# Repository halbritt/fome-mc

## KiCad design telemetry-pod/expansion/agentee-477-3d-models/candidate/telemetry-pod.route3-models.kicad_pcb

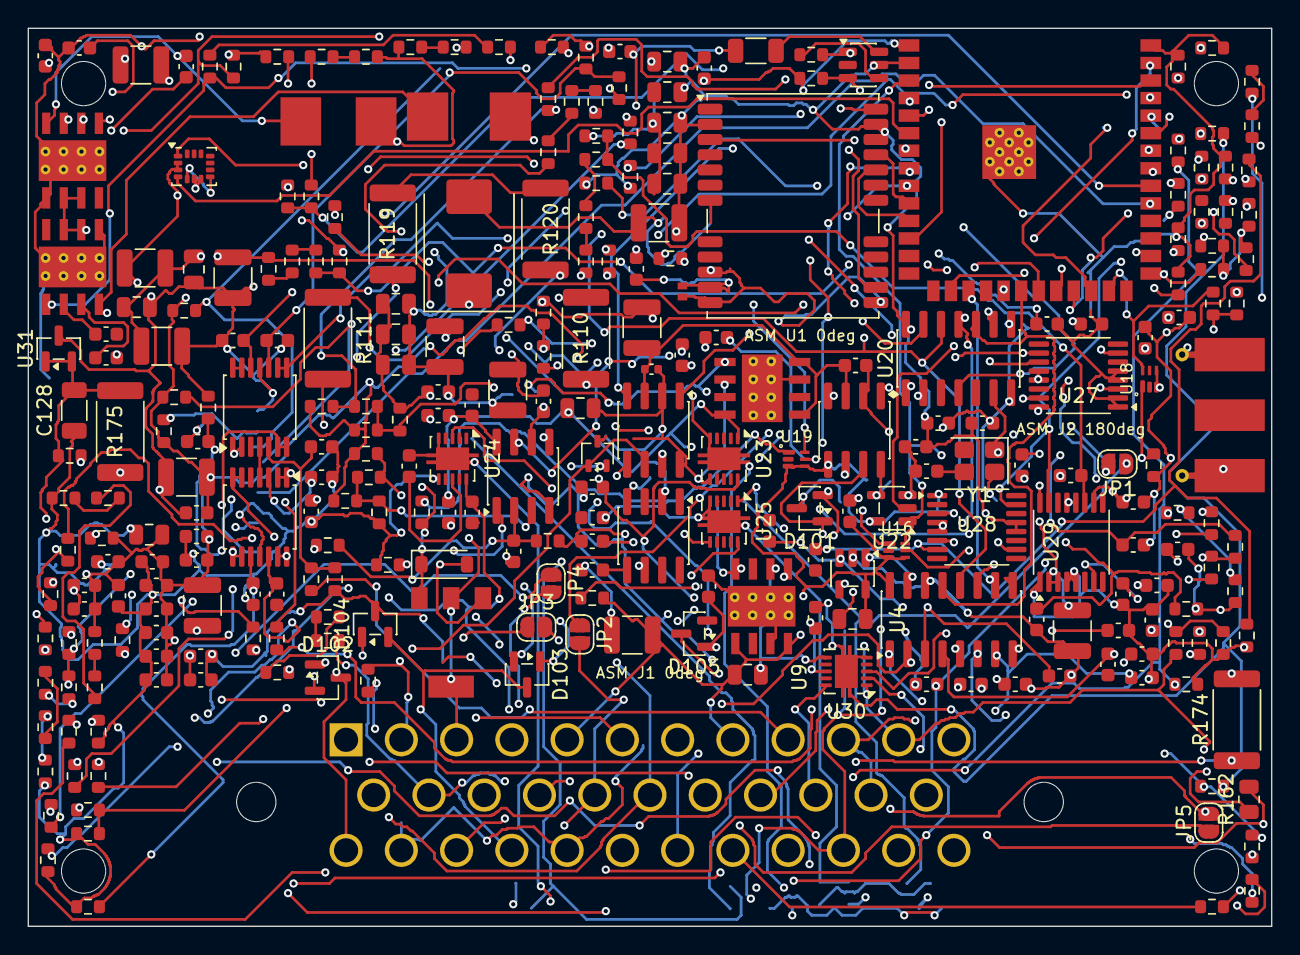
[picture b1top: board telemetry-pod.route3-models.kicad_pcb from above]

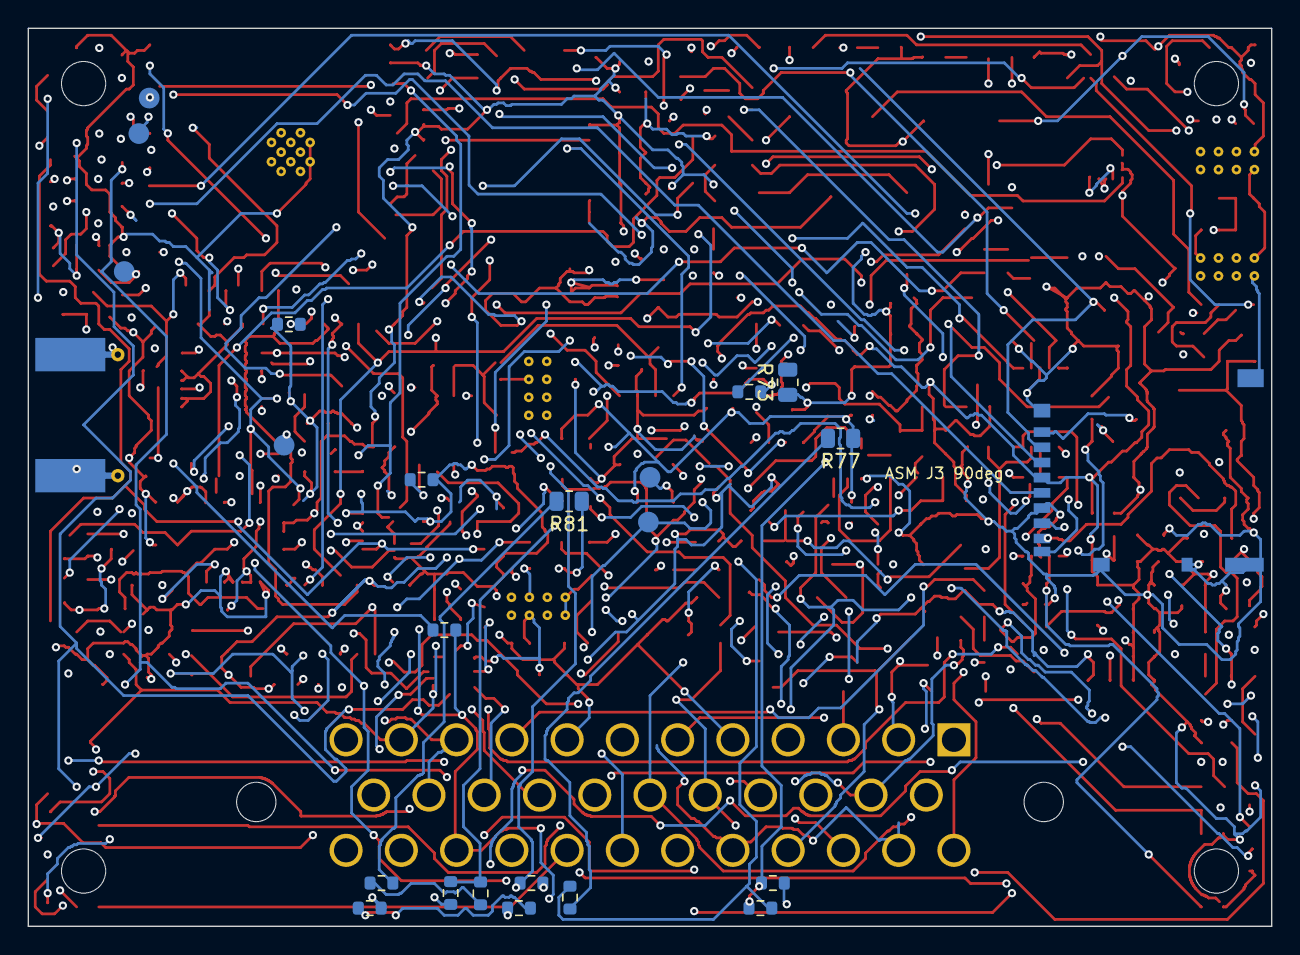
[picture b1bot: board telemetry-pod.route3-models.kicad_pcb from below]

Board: 4 copper layers, 90.0 x 65.0 mm, 309 parts (23 on the bottom side), 182 nets.

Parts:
C1, C2, C8, C9: 4.7 uF/100 V; C_1210_3225Metric
C3, C10: 220 nF/100 V; C_0805_2012Metric
C4, C11, C16, C18, C20, C21, C22, C44: 1 uF/16 V; C_0603_1608Metric
C5, C12, C30, C32, C34, C36, C38, C39, C41, C42, C43, C54, C56, C58, C60: 100 nF/50 V X7R; C_0603_1608Metric
C6, C7, C13, C14, C15, C17, C19: 22 uF/25 V; C_1210_3225Metric
C31, C33, C35, C37, C55, C57, C59, C61: 100 pF C0G/50 V; C_0603_1608Metric
C40: 470 pF C0G/50 V; C_0603_1608Metric
C45: 22uF; C_1210_3225Metric
C46, C48, C49, C51, C53, C62, C65, C72, C76, C78, C79, C83, C84, C85: 100nF; C_0603_1608Metric
C47: 10nF; C_0603_1608Metric
C50, C52, C80: 1uF; C_0603_1608Metric
C64: 4.7 uF/16 V X7R; C_0805_2012Metric
C71, C75, C77: 22nF; C_0603_1608Metric
C81, C82: 18pF C0G; C_0603_1608Metric
C86, C89, C92, C98, C118, C119, C120, C121, C122, C123, C124: 1uF 50V X7R; C_0805_2012Metric
C87, C90, C93, C97, C110, C111, C112, C114, C115, C116, C117, C125, C127, C129: 100nF 50V X7R; C_0603_1608Metric
C88, C91, C94, C126: 10nF 50V C0G 10%; C_0603_1608Metric
C95, C96: 220pF C0G; C_0603_1608Metric
C100: 100n; C_0402_1005Metric
C128: 10uF 16V X7R; C_1206_3216Metric
D1: SMCJ24CA; D_SMC
D2: BZT52C12-7-F; D_SOD-123
D3: PESD5V0C1BLS-QYL; SOD882BD
D100: PESD1CAN-UX; SOT-323_SC-70
D101, D104: PESD2CANFD24V-TR; SOT-23
D102, D103, D105: BAV199,215; SOT-23
H1, H2, H3, H4: MountingHole; AgentEE_Mechanical_MountingHole_NPTH
J1: 1-776163-1; AMPSEAL_35_1-776163-1
J2: 732511150; SMA_Molex_73251-1153_EdgeMount_Horizontal
J3: DM3AT-SF-PEJM5; microSD_HC_Hirose_DM3AT-SF-PEJM5
JP1: TIRE_TERM_CLOSE_ONLY_AT_BUS_END; SolderJumper-2_P1.3mm_Open_RoundedPad1.0x1.5mm
JP2: AUX1_THERM_PULLUP_CLOSE_TO_ENABLE; SolderJumper-2_P1.3mm_Open_RoundedPad1.0x1.5mm
JP3: AUX2_THERM_PULLUP_CLOSE_TO_ENABLE; SolderJumper-2_P1.3mm_Open_RoundedPad1.0x1.5mm
JP4: AUX3_THERM_PULLUP_CLOSE_TO_ENABLE; SolderJumper-2_P1.3mm_Open_RoundedPad1.0x1.5mm
JP5: AUX4_THERM_PULLUP_CLOSE_TO_ENABLE; SolderJumper-2_P1.3mm_Open_RoundedPad1.0x1.5mm
L1: 15 uH; SRP7050TA
L2: 6.8 uH; SRP7050WA
L3: LQW18AN56NJ00D; L_0603_1608Metric
Q1: DMP6023LE-13; DMP6023LE_SOT223
R1, R24, R25, R29: 100 kohm; R_0603_1608Metric
R2: 51 kohm; R_0603_1608Metric
R3, R5, R10, R11, R13, R14, R16, R17, R19, R20, R22, R23, R34, R35, R37, R38, R40, R41, R43, R44, R46, R47, R48, R49, R50, R55, R64, R65, R66, R67, R68, R69, R71, R72: 10 kohm; R_0603_1608Metric
R4: 22 kohm; R_0603_1608Metric
R6: 47 kohm; R_0603_1608Metric
R7: 1 ohm; R_0603_1608Metric
R12, R15, R18, R21, R36, R39, R42, R45, R118, R127: 100 ohm; R_0603_1608Metric
R26: 10 ohm/0.25 W; R_1206_3216Metric
R27: 2 kohm; R_0603_1608Metric
R28: 1 kohm; R_0603_1608Metric
R30, R31, R32, R33: 10k; R_0603_1608Metric
R56: 16.9 kohm 0.1%; R_0603_1608Metric
R57, R61, R63, R112, R113, R115, R121, R122, R124: 10 kohm 0.1%; R_0603_1608Metric
R60: 30.1 kohm 0.1% 25ppm/K; R_0603_1608Metric
R62: 64.9 kohm 0.1%; R_0603_1608Metric
R70: 120 ohm; R_0603_1608Metric
R73, R77, R81, R162: 1.05 Mohm 0.1% 25ppm/K; R_0805_2012Metric
R74, R78, R82: 68.1 kohm 0.1% 25ppm/K; R_0603_1608Metric
R75, R79, R83: 215 kohm 0.1% 25ppm/K; R_0603_1608Metric
R76, R80: 44.2 kohm 0.1%; R_0603_1608Metric
R84: 26.7 kohm 0.1%; R_0603_1608Metric
R100: 120; R_0603_1608Metric
R110, R111, R119, R120: 620 ohm; R_2512_6332Metric
R114, R123: 56 kohm 0.1%; R_0603_1608Metric
R116, R125: 100 kohm 0.1%; R_0603_1608Metric
R117, R126: 4.7 kohm 1%; R_0603_1608Metric
R128, R129, R130, R132, R133, R134, R136, R137, R138, R144, R145, R146, R148, R149, R150, R152, R153, R154, R156, R157, R158, R166, R167, R168: 499 kohm 0.1% 25ppm/C; R_0603_1608Metric
R131, R135, R139, R147, R151, R155, R159, R169: 4.99 kohm 0.1% 25ppm/C; R_0603_1608Metric
R160, R161: 2.2 kohm 1% 100ppm/C; R_0603_1608Metric
R163: 95.3 kohm 0.1% 25ppm/K; R_0603_1608Metric
R164: 287 kohm 0.1% 25ppm/K; R_0603_1608Metric
R165: 44.2 kohm 0.1% 25ppm/K; R_0603_1608Metric
R170, R171, R172, R173: 10 kohm 0.1% 25ppm/K; R_0603_1608Metric
R174, R175: 200 ohm 1% 100ppm/K 1.5W CRCW2512-HP; R_2512_6332Metric
R176, R177, R178: 499 kohm 0.1% 25ppm/K; R_0603_1608Metric
R179: 4.99 kohm 0.1% 25ppm/K; R_0603_1608Metric
R180: 100 kohm 1% 100ppm/K; R_0603_1608Metric
R181: 1.2 kohm 0.1% 25ppm/K; R_0603_1608Metric
TP1: POD_UART_TX; PogoPad_D1.5mm
TP2: POD_UART_RX; PogoPad_D1.5mm
TP3: GND; PogoPad_D1.5mm
TP4: MCU_EN; PogoPad_D1.5mm
TP5: MCU_BOOT; PogoPad_D1.5mm
TP6: +3V3; PogoPad_D1.5mm
U1: ESP32-S3-WROOM-1-N8; ESP32-S3-WROOM-1
U2: LSM6DSO32TR; LGA-14_3x2.5mm_P0.5mm_LayoutBorder3x4y
U3: NEO-M9N-00B; ublox_NEO
U4: MCP3208-BI/SL; SOIC-16_3.9x9.9mm_P1.27mm
U5, U7: LMR36520ADDAR; DDA0008B
U6, U12: TPS7B4253QDDARQ1; DDA0008J_C02
U8, U13: ADA4096-4ARUZ-R7; TSSOP-14_4.4x5mm_P0.65mm
U9: OPA320AIDBVR; SOT-23-5
U10: TPS2553QDBVRQ1; SOT-23-6
U11: REF5050AIDR; SOIC-8_3.9x4.9mm_P1.27mm
U16, U18, U19: TPS389001DSER; DSE0006A
U20: MCP2518FDT-E/SL; SOIC-14_3.9x8.7mm_P1.27mm
U21: TJA1051T/3/1J; SOIC-8_3.9x4.9mm_P1.27mm
U22: SN74LVC1G132DBVR; SOT-23-5
U23, U24, U25, U30: TPS26625DRCR; VSON-10-1EP_3x3mm_P0.5mm_EP1.65x2.4mm
U26: LM2903BQDRQ1; SOIC-8_3.9x4.9mm_P1.27mm
U27, U28, U29: ADS1119IPWR; TSSOP-16_4.4x5mm_P0.65mm
U31: TL431BQDBZR; SOT-23
U100: TJA1051T-3; SOIC-8_3.9x4.9mm_P1.27mm
Y1: X1E0003410031 20MHz 12pF; Crystal_SMD_SeikoEpson_FA238-4Pin_3.2x2.5mm

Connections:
/+3V3: C13.1, C14.1, C15.1, C38.1, C41.1, C43.1, C44.1, C45.1, C46.1, C48.1, C49.1, C50.1, C51.1, C52.1, C53.1, C62.1, C64.1, C65.1, C72.1, C76.1, C78.1, C79.1, C80.1, C84.1, C85.1, C118.1, C119.1, C120.1, C121.1, C122.1, C123.1, J3.4, L2.2, R4.1, R25.2, R29.1, R30.1, R31.1, R32.1, R46.1, R47.1, R48.1, R49.1, R50.1, R55.2, R56.1, R64.1, R65.1, R66.1, R67.1, R69.1, R71.1, R114.1, R117.1, R123.1, R126.1, R136.1, R160.1, R161.1, TP6.1, U1.2, U2.5, U2.8, U3.2, U3.22, U3.23, U4.16, U8.4, U9.5, U10.1, U10.5, U13.4, U16.3, U16.4, U18.3, U18.4, U19.3, U19.4, U20.14, U21.5, U22.5, U27.3, U27.12, U27.13, U28.1, U28.3, U28.12, U28.13, U29.2, U29.3, U29.12, U29.13, U100.5
/+5V_CAN: C19.1, C83.1, C100.1, U12.1, U12.4, U21.3, U100.3
/ADC_AIN0: C31.1, R12.2, U4.1
/ADC_AIN1: C33.1, R15.2, U4.2
/ADC_AIN2: C35.1, R18.2, U4.3
/ADC_AIN3: C37.1, R21.2, U4.4
/ADC_AIN4: C55.1, R36.2, U4.5
/ADC_AIN5: C57.1, R39.2, U4.6
/ADC_AIN6: C59.1, R42.2, U4.7
/ADC_AIN7: C61.1, R45.2, U4.8
/ADC_CS: R32.2, U1.17, U4.10
/AFE_BUF0: R12.1, U8.1, U8.2
/AFE_BUF1: R15.1, U8.6, U8.7
/AFE_BUF2: R18.1, U8.8, U8.9
/AFE_BUF3: R21.1, U8.13, U8.14
/AFE_BUF4: R36.1, U13.1, U13.2
/AFE_BUF5: R39.1, U13.6, U13.7
/AFE_BUF6: R42.1, U13.8, U13.9
/AFE_BUF7: R45.1, U13.13, U13.14
/AFE_DIV0: C30.1, R10.2, R11.1, U8.3
/AFE_DIV1: C32.1, R13.2, R14.1, U8.5
/AFE_DIV2: C34.1, R16.2, R17.1, U8.10
/AFE_DIV3: C36.1, R19.2, R20.1, U8.12
/AFE_DIV4: C54.1, R34.2, R35.1, U13.3
/AFE_DIV5: C56.1, R37.2, R38.1, U13.5
/AFE_DIV6: C58.1, R40.2, R41.1, U13.10
/AFE_DIV7: C60.1, R43.2, R44.1, U13.12
/ANT_BIAS: C42.1, L3.1, R26.2
/ANT_LIMITED: R26.1, U10.6
/BOOT_3V3: C12.1, U7.7
/BOOT_PRE: C5.1, U5.7
/DIAG_I2C_SCL: R161.2, U1.23, U27.16, U28.16, U29.16
/DIAG_I2C_SDA: R160.2, U1.22, U27.15, U28.15, U29.15
/DIAG_U27_AIN0: C110.1, R130.2, R131.1, U27.11
/DIAG_U27_AIN0_UPPER1: R128.2, R129.1
/DIAG_U27_AIN0_UPPER2: R129.2, R130.1
/DIAG_U27_AIN1: C111.1, R134.2, R135.1, U27.10
/DIAG_U27_AIN1_UPPER1: R132.2, R133.1
/DIAG_U27_AIN1_UPPER2: R133.2, R134.1
/DIAG_U27_AIN2: C112.1, R138.2, R139.1, U27.7
/DIAG_U27_AIN2_UPPER1: R136.2, R137.1
/DIAG_U27_AIN2_UPPER2: R137.2, R138.1
/DIAG_U28_AIN1: C114.1, R146.2, R147.1, U28.10
/DIAG_U28_AIN1_UPPER1: R144.2, R145.1
/DIAG_U28_AIN1_UPPER2: R145.2, R146.1
/DIAG_U28_AIN2: C127.1, R168.2, R169.1, U28.7
/DIAG_U28_AIN2_UPPER1: R166.2, R167.1
/DIAG_U28_AIN2_UPPER2: R167.2, R168.1
/DIAG_U28_AIN3: C129.1, R178.2, R179.1, U28.6
/DIAG_U28_AIN3_UPPER1: R176.2, R177.1
/DIAG_U28_AIN3_UPPER2: R177.2, R178.1
/DIAG_U29_AIN0: C115.1, R150.2, R151.1, U29.11
/DIAG_U29_AIN0_UPPER1: R148.2, R149.1
/DIAG_U29_AIN0_UPPER2: R149.2, R150.1
/DIAG_U29_AIN1: C116.1, R154.2, R155.1, U29.10
/DIAG_U29_AIN1_UPPER1: R152.2, R153.1
/DIAG_U29_AIN1_UPPER2: R153.2, R154.1
/DIAG_U29_AIN2: C117.1, R158.2, R159.1, U29.7
/DIAG_U29_AIN2_UPPER1: R156.2, R157.1
/DIAG_U29_AIN2_UPPER2: R157.2, R158.1
/FB_3V3: R5.1, R28.2, U7.5
/FB_3V3_SERIES: R4.2, R28.1
/FB_PRE: R3.1, R27.2, U5.5
/FB_PRE_SERIES: R2.2, R27.1
/GND: C1.2, C2.2, C3.2, C4.2, C6.2, C7.2, C8.2, C9.2, C10.2, C11.2, C13.2, C14.2, C15.2, C16.2, C17.2, C18.2, C19.2, C20.2, C21.2, C22.2, C30.2, C31.2, C32.2, C33.2, C34.2, C35.2, C36.2, C37.2, C38.2, C39.2, C40.2, C41.2, C42.2, C43.2, C44.2, C45.2, C46.2, C47.2, C48.2, C49.2, C50.2, C51.2, C52.2, C53.2, C54.2, C55.2, C56.2, C57.2, C58.2, C59.2, C60.2, C61.2, C62.2, C64.2, C65.2, C71.2, C72.2, C75.2, C76.2, C77.2, C78.2, C79.2, C80.2, C81.2, C82.2, C83.2, C84.2, C85.2, C86.2, C87.2, C89.2, C90.2, C92.2, C93.2, C95.2, C96.2, C97.2, C98.2, C100.2, C110.2, C111.2, C112.2, C114.2, C115.2, C116.2, C117.2, C118.2, C119.2, C120.2, C121.2, C122.2, C123.2, C124.2, C125.2, C127.2, C128.2, C129.2, D1.2, D3.2, D100.3, D101.3, D104.3, J1.4, J1.7, J1.10, J1.13, J1.16, J1.22, J1.25, J1.28, J1.32, J2.2, J3.6, J3.10, J3.SH, R1.2, R3.2, R5.2, R6.2, R11.2, R14.2, R17.2, R20.2, R23.2, R24.2, R33.2, R35.2, R38.2, R41.2, R44.2, R57.2, R61.2, R63.2, R68.2, R72.2, R113.2, R115.2, R122.2, R124.2, R131.2, R135.2, R139.2, R147.2, R151.2, R155.2, R159.2, R169.2, R179.2, R180.2, TP3.1, U1.1, U1.40, U1.41, U2.2, U2.3, U2.6, U2.7, U3.7, U3.10, U3.12, U3.13, U3.24, U4.9, U4.14, U5.1, U5.9, U6.3, U6.6, U6.9, U7.1, U7.9, U8.11, U9.2, U10.2, U11.4, U12.3, U12.6, U12.9, U13.11, U16.2, U18.2, U19.2, U20.7, U21.2, U22.3, U23.6, U24.6, U25.6, U26.4, U27.1, U27.2, U27.4, U27.5, U28.2, U28.4, U28.5, U29.1, U29.4, U29.5, U30.6, U31.3, U100.2, U100.8, Y1.2, Y1.4
/GNSS_ANT_FAULT_N: R25.1, U10.4
/GNSS_LNA_EN: R24.1, U3.14, U10.3
/GNSS_PPS: U1.7, U3.3
/GNSS_RX_IN: U1.10, U3.21
/GNSS_TX_OUT: U1.11, U3.20
/IMU_CS: R31.2, U1.18, U2.12
/IMU_INT1: U1.6, U2.4
/MCU_BOOT: R30.2, TP5.1, U1.27
/MCU_BOOT46: R33.1, U1.16
/MCU_EN: C47.1, R29.2, TP4.1, U1.3, U16.6, U22.1
/POD_5V_AUX: C125.1, D105.1, J1.21, R166.1, R180.1, U30.10
/POD_5V_SENSOR: C17.1, C124.1, J1.5, J1.8, J1.11, J1.14, R6.1, R22.1, R60.1, R144.1, R162.1, U6.1, U6.4, U30.1
/POD_12V_IN: D1.1, J1.3, Q1.2
/POD_12V_PROTECTED: C1.1, C2.1, C3.1, C8.1, C9.1, C10.1, D2.1, Q1.3, R62.1, R128.1, U5.2, U5.3, U7.2, U7.3
/POD_AUX1_SIGNAL: J1.17, JP2.2, R34.1
/POD_AUX2_SIGNAL: J1.18, JP3.2, R37.1
/POD_AUX3_SIGNAL: J1.19, JP4.2, R40.1
/POD_AUX4_SIGNAL: J1.20, JP5.2, R43.1
/POD_CAN_N: D100.1, J1.2, R100.2, U100.6
/POD_CAN_P: D100.2, J1.1, R100.1, U100.7
/POD_FRONT_BRAKE_SIGNAL: J1.12, R16.1
/POD_FRONT_FORK_SIGNAL: J1.6, R10.1
/POD_GNSS_RF: D3.1, J2.1, L3.2, U3.11
/POD_REAR_BRAKE_SIGNAL: J1.15, R19.1
/POD_REAR_SHOCK_SIGNAL: J1.9, R13.1
/POD_TIRE_SUPPLY: C93.1, J1.31, R156.1, U25.10
/POD_UART_RX: TP2.1, U1.36
/POD_UART_TX: TP1.1, U1.37
/POD_WHEEL_FRONT_SIGNAL: D102.3, D104.1, J1.24
/POD_WHEEL_FRONT_SUPPLY: C87.1, J1.23, R110.1, R148.1, U23.10
/POD_WHEEL_REAR_SIGNAL: D103.3, D104.2, J1.27
/POD_WHEEL_REAR_SUPPLY: C90.1, J1.26, R119.1, R152.1, U24.10
/POWER_FAIL_N: R65.2, U1.12, U19.6
/PRE_6V3: C6.1, C7.1, C16.1, C18.1, C20.1, C86.1, C89.1, C92.1, C97.1, C98.1, L1.2, R2.1, R73.1, R77.1, R81.1, R132.1, U6.8, U11.2, U12.8, U23.1, U24.1, U25.1, U26.8
/REF_CAP_NODE: C22.1, R7.2
/REF_DIV: C39.1, R22.2, R23.1, U9.3
/REF_NR: C21.1, U11.5
/REVERSE_GATE: D2.2, Q1.1, R1.1
/SD_CD: J3.9, R55.1, U1.28
/SD_CLK: J3.5, U1.31
/SD_CMD: J3.3, R46.2, U1.32
/SD_DAT0: J3.7, R47.2, U1.33
/SD_DAT1: J3.8, R48.2, U1.34
/SD_DAT2: J3.1, R49.2, U1.35
/SD_DAT3: J3.2, R50.2, U1.24
/SENSOR_FAULT_N: R64.2, U1.25, U18.6
/SENSOR_POWER_AUX_DVDT: C126.1, U30.8
/SENSOR_POWER_AUX_ILIM: R165.1, U30.7
/SENSOR_POWER_AUX_OVP: R163.2, R164.1, U30.3
/SENSOR_POWER_AUX_RTN: C126.2, R164.2, R165.2, U30.5, U30.11
/SENSOR_POWER_AUX_UVLO: R162.2, R163.1, U30.2
/SENSOR_POWER_FRONT_DVDT: C88.1, U23.8
/SENSOR_POWER_FRONT_ILIM: R76.1, U23.7
/SENSOR_POWER_FRONT_OVP: R74.2, R75.1, U23.3
/SENSOR_POWER_FRONT_RTN: C88.2, R75.2, R76.2, U23.5, U23.11
/SENSOR_POWER_FRONT_UVLO: R73.2, R74.1, U23.2
/SENSOR_POWER_REAR_DVDT: C91.1, U24.8
/SENSOR_POWER_REAR_ILIM: R80.1, U24.7
/SENSOR_POWER_REAR_OVP: R78.2, R79.1, U24.3
/SENSOR_POWER_REAR_RTN: C91.2, R79.2, R80.2, U24.5, U24.11
/SENSOR_POWER_REAR_UVLO: R77.2, R78.1, U24.2
/SENSOR_POWER_TIRE_DVDT: C94.1, U25.8
/SENSOR_POWER_TIRE_ILIM: R84.1, U25.7
/SENSOR_POWER_TIRE_OVP: R82.2, R83.1, U25.3
/SENSOR_POWER_TIRE_RTN: C94.2, R83.2, R84.2, U25.5, U25.11
/SENSOR_POWER_TIRE_UVLO: R81.2, R82.1, U25.2
/SENSOR_REF_2V5: C40.1, U4.15, U9.1, U9.4
/SETPOINT_5V: R7.1, U6.5, U11.6, U12.5
/SPI_MISO: U1.21, U2.1, U4.12, U20.12
/SPI_MOSI: U1.19, U2.14, U4.11, U20.11
/SPI_SCK: U1.20, U2.13, U4.13, U20.10
/SUP_U16_CT: C71.1, U16.5
/SUP_U16_SENSE: R56.2, R57.1, U16.1
/SUP_U18_CT: C75.1, U18.5
/SUP_U18_SENSE: R61.1, R181.2, U18.1
/SUP_U18_TOP_SERIES: R60.2, R181.1
/SUP_U19_CT: C77.1, U19.5
/SUP_U19_SENSE: R62.2, R63.1, U19.1
/SW_3V3: C12.2, L2.1, U7.8
/SW_PRE: C5.2, L1.1, U5.8
/THERM_AUX1_SELECT: JP2.1, R170.2
/THERM_AUX2_SELECT: JP3.1, R171.2
/THERM_AUX3_SELECT: JP4.1, R172.2
/THERM_AUX4_SELECT: JP5.1, R173.2
/THERM_BIAS_IN: D105.3, R174.1
/THERM_BIAS_MID: R174.2, R175.1
/THERM_EXC_2V495: C128.1, R170.1, R171.1, R172.1, R173.1, R175.2, R176.1, U31.1, U31.2
/TIRE_CAN_CS: R66.2, U1.8, U20.13
/TIRE_CAN_GPIO1: R72.1, U20.8
/TIRE_CAN_H: D101.1, J1.29, J1.33, R70.1, U21.7
/TIRE_CAN_INT_N: R67.2, U1.9, U20.4
/TIRE_CAN_L: D101.2, J1.30, J1.34, JP1.2, U21.6
/TIRE_CAN_OSC1: C81.1, U20.6, Y1.1
/TIRE_CAN_OSC2: C82.1, U20.5, Y1.3
/TIRE_CAN_RX: U20.2, U21.4
/TIRE_CAN_SILENT: R71.2, U21.8, U22.4
/TIRE_CAN_TERM: JP1.1, R70.2
/TIRE_CAN_TX: R69.2, U20.1, U21.1
/TIRE_CAN_TX_ENABLE: R68.1, U20.9, U22.2
/TWAI_RX: U1.5, U100.4
/TWAI_TX: U1.4, U100.1
/VCC_3V3: C11.1, U7.6
/VCC_PRE: C4.1, U5.6
/WHEEL_FRONT_CAPTURE: R118.2, U1.39
/WHEEL_FRONT_DIODE_OUT: D102.2, R112.1
/WHEEL_FRONT_FILTERED: C95.1, R112.2, R113.1, U26.2
/WHEEL_FRONT_OUT: R116.1, R117.2, R118.1, U26.1
/WHEEL_FRONT_PULLUP: D102.1, R111.2
/WHEEL_FRONT_PULLUP_MID: R110.2, R111.1
/WHEEL_FRONT_THRESHOLD: R114.2, R115.1, R116.2, U26.3
/WHEEL_REAR_CAPTURE: R127.2, U1.38
/WHEEL_REAR_DIODE_OUT: D103.2, R121.1
/WHEEL_REAR_FILTERED: C96.1, R121.2, R122.1, U26.6
/WHEEL_REAR_OUT: R125.1, R126.2, R127.1, U26.7
/WHEEL_REAR_PULLUP: D103.1, R120.2
/WHEEL_REAR_PULLUP_MID: R119.2, R120.1
/WHEEL_REAR_THRESHOLD: R123.2, R124.1, R125.2, U26.5
